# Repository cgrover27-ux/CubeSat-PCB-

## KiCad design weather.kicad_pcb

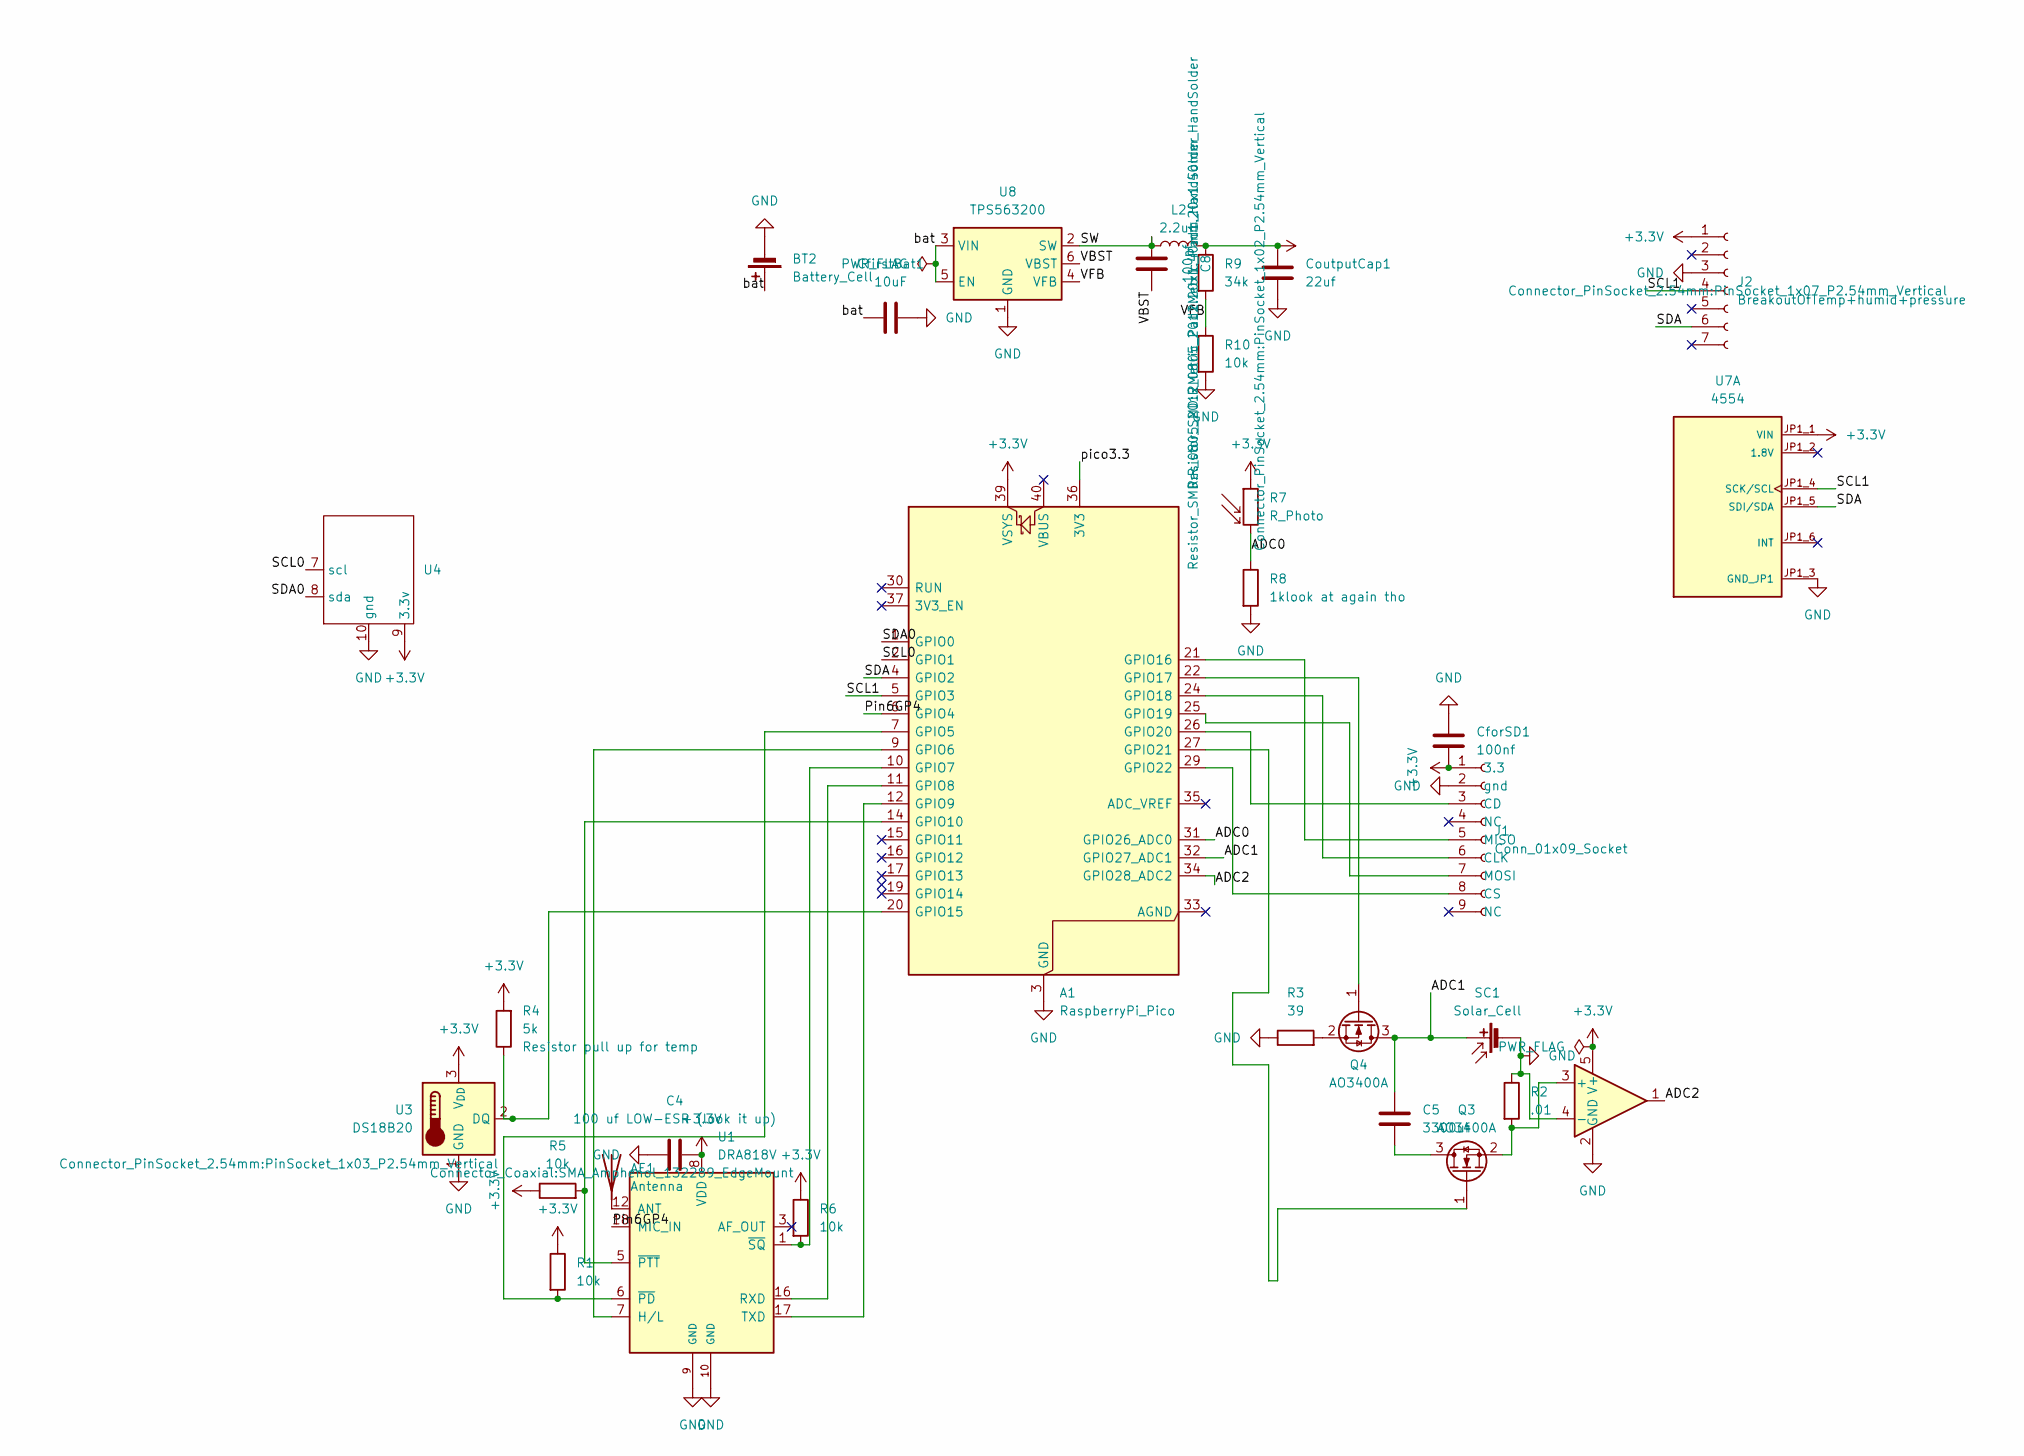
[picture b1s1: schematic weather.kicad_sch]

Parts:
A1: RaspberryPi_Pico; RaspberryPi_Pico_Common_Unspecified
AE1: Antenna; SMA_Amphenol_132289_EdgeMount
BT2: Battery_Cell
C4: 100 uf LOW-ESR (look it up)
C5: 3300uf; CP_Radial_D12.5mm_P5.00mm
C8: 100nf; C_0805_2012Metric_Pad1.18x1.45mm_HandSolder
CfirstBat1: 10uF; C_0805_2012Metric_Pad1.18x1.45mm_HandSolder
CforSD1: 100nf; C_0805_2012Metric_Pad1.18x1.45mm_HandSolder
CoutputCap1: 22uf; C_0805_2012Metric_Pad1.18x1.45mm_HandSolder
J1: Conn_01x09_Socket; PinHeader_1x09_P2.54mm_Vertical
J2: BreakoutOfTemp+humid+pressure; PinSocket_1x07_P2.54mm_Vertical
L2: 2.2uH; L_0805_2012Metric_Pad1.05x1.20mm_HandSolder
Q3, Q4: AO3400A; SOT-23
R1, R5, R6, R10: 10k; R_0805_2012Metric_Pad1.20x1.40mm_HandSolder
R2: .01; R_0805_2012Metric_Pad1.20x1.40mm_HandSolder
R3: 39; R_0805_2012Metric_Pad1.20x1.40mm_HandSolder
R4: 5k; R_0805_2012Metric_Pad1.20x1.40mm_HandSolder
R7: R_Photo; PinSocket_1x02_P2.54mm_Vertical
R8: 1klook at again tho; R_0805_2012Metric_Pad1.20x1.40mm_HandSolder
R9: 34k; R_0805_2012Metric_Pad1.20x1.40mm_HandSolder
SC1: Solar_Cell; TestPoint_2Pads_Pitch5.08mm_Drill1.3mm
U1: DRA818V; VHF_UHF_Module_generic
U3: DS18B20; PinSocket_1x03_P2.54mm_Vertical
U4: SparkFun GNSS Receiver Breakout - MAX-M10S (Qwiic)
U5: INA180A3; SOT-23-5
U7: 4554; MODULE_4554; PARTREV N/A
U8: TPS563200; SOT-23-6

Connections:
+3.3V: A1.39 (VSYS), C4.2, CforSD1.2, CoutputCap1.2, J1.1 (3.3), J2.1 (blk), L2.2, R1.1, R4.2, R5.1, R6.1, R7.1, R9.1, U1.8 (VDD), U3.3 (V_{DD}), U4.9 (3.3v), U5.5 (V+), U7.JP1_1 (VIN)
/ADC0: A1.31 (GPIO26_ADC0), R7.2, R8.1
/ADC1: A1.32 (GPIO27_ADC1), C5.1, Q4.3 (D), SC1.1 (+)
/ADC2: A1.34 (GPIO28_ADC2), U5.1
/Pin6GP4: A1.6 (GPIO4), U1.18 (MIC_IN)
/SCL0: A1.2 (GPIO1), U4.7 (scl)
/SCL1: A1.5 (GPIO3), J2.4 (sda), U7.JP1_4 (SCK/SCL)
/SDA: A1.4 (GPIO2), J2.6 (vcc), U7.JP1_5 (SDI/SDA)
/SDA0: A1.1 (GPIO0), U4.8 (sda)
/SW: C8.1, L2.1, U8.2 (SW)
/VBST: C8.2, U8.6 (VBST)
/VFB: R9.2, R10.1, U8.4 (VFB)
/bat: BT2.1 (+), CfirstBat1.1, U8.3 (VIN), U8.5 (EN)
/pico3.3: A1.36 (3V3)
GND: A1.3 (GND), A1.8 (GND), A1.13 (GND), A1.18 (GND), A1.23 (GND), A1.28 (GND), A1.38 (GND), BT2.2 (-), C4.1, CfirstBat1.2, CforSD1.1, CoutputCap1.1, J1.2 (gnd), J2.3 (res), R2.1, R3.1, R8.2, R10.2, SC1.2 (-), U1.9 (GND), U1.10 (GND), U3.1 (GND), U4.10 (gnd), U5.2 (GND), U5.4 (-), U7.JP1_3 (GND_JP1), U8.1 (GND)
unnamed: A1.7 (GPIO5), R1.2, U1.6 (~PD)
unnamed: A1.9 (GPIO6), U1.7 (H/L)
unnamed: A1.10 (GPIO7), R6.2, U1.1 (~SQ)
unnamed: A1.11 (GPIO8), U1.16 (RXD)
unnamed: A1.12 (GPIO9), U1.17 (TXD)
unnamed: A1.14 (GPIO10), R5.2, U1.5 (~PTT)
unnamed: A1.20 (GPIO15), R4.1, U3.2 (DQ)
unnamed: A1.21 (GPIO16), J1.5 (MISO)
unnamed: A1.22 (GPIO17), Q4.1 (G)
unnamed: A1.24 (GPIO18), J1.6 (CLK)
unnamed: A1.25 (GPIO19), J1.7 (MOSI)
unnamed: A1.26 (GPIO20), J1.3 (CD)
unnamed: A1.27 (GPIO21), Q3.1 (G)
unnamed: A1.29 (GPIO22), J1.8 (CS)
unnamed: AE1.1 (A_1), U1.12 (ANT)
unnamed: C5.2, Q3.3 (D)
unnamed: Q3.2 (S), R2.2, U5.3 (+)
unnamed: Q4.2 (S), R3.2

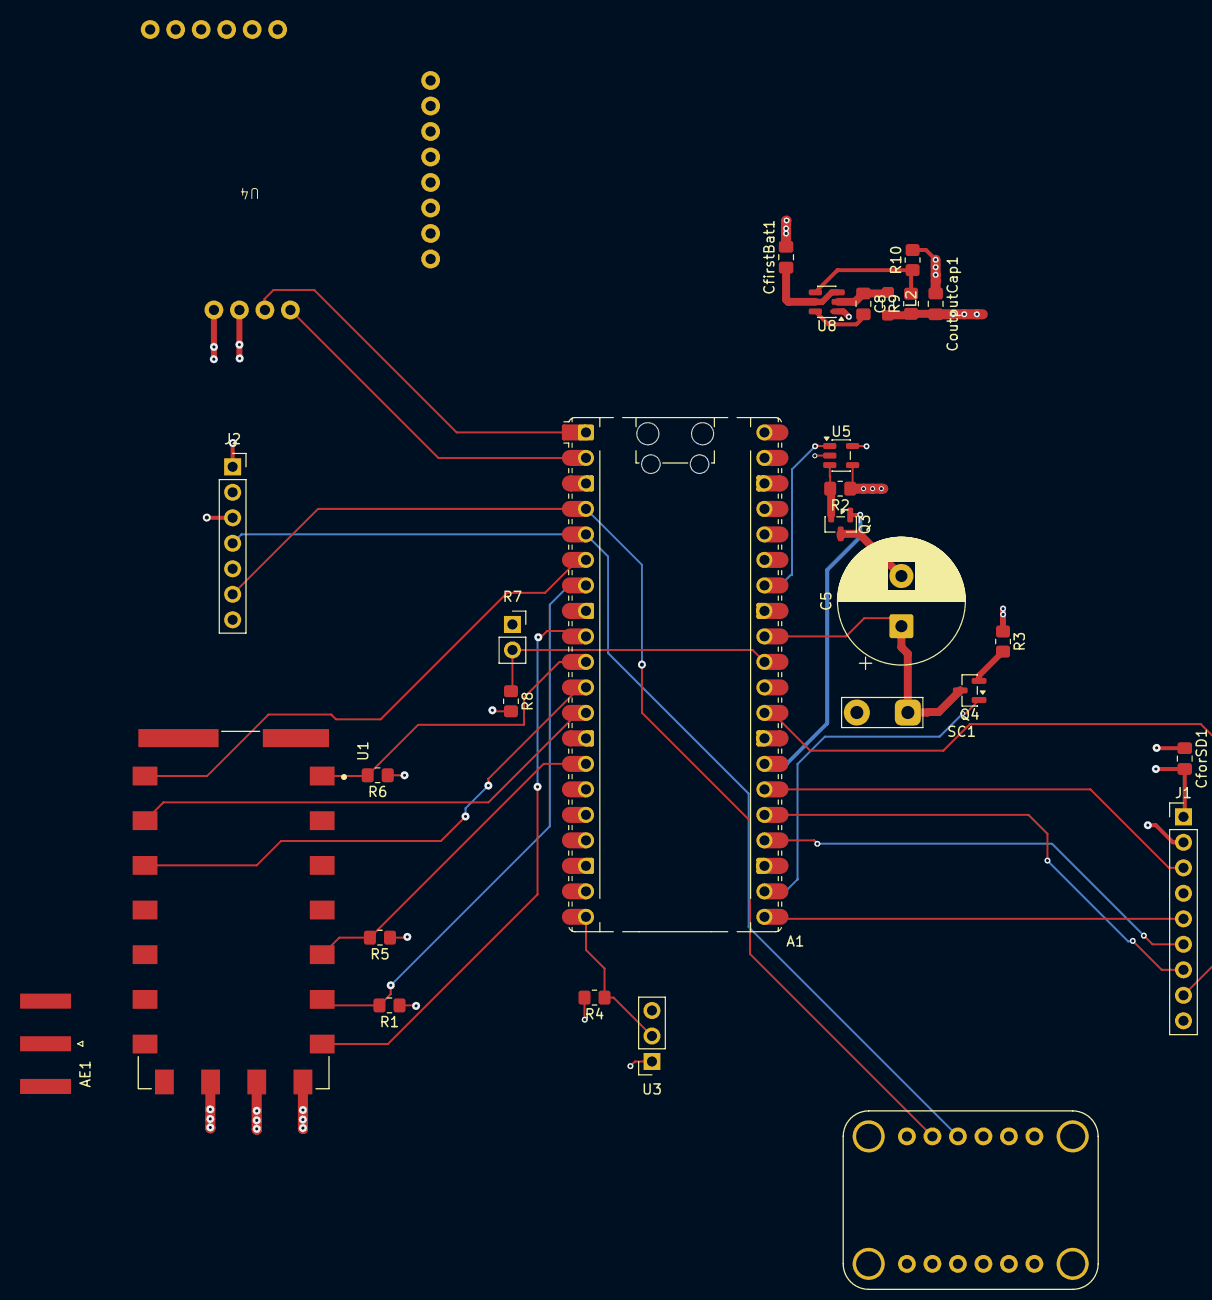
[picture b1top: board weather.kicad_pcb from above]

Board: 4 copper layers, 29 parts (0 on the bottom side), 32 nets.
